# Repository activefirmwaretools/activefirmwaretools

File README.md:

# Active Firmware Tools

**Record. Reveal. Refine.**

The official repository for the Active-Pro Debugger and Logic Analyzer family — the recorder of embedded system behavior.

[Download](https://activefirmwaretools.com/download) · [User's Manual](https://activefirmwaretools.com/usersmanual) · [Store](https://activefirmwaretools.com/store) · [Blog](https://activefirmwaretools.com/active-firmware-tools-blog)

---

## What is Active-Pro?

Active-Pro is a hardware-and-software toolchain that records what your embedded system is actually doing — every signal transition, every protocol event, every stretch of idle time — and lets you replay, inspect, and share that capture later.

Think of it as Wireshark for the wires on your board. Where a logic analyzer shows you waveforms and a debugger shows you breakpoints, Active-Pro records the full behavioral trace of a running system so you can see how the pieces actually fit together over time.

Three products share the same application and capture format:

- **Active Debugger** — entry-level debug port and signal capture
- **Active-Pro** — full debugger and logic analyzer
- **Active-Pro Ultra** — super-speed capture for higher-bandwidth and longer-duration traces

All three work with the free Active-Pro application on Windows, macOS, and Linux. Run the app without hardware attached to demo every feature.

## What's in this repo

| Folder | Contents |
|---|---|
| [`active-debug-port-source-code`](./active-debug-port-source-code) | Reference source for the Active debug port |
| [`active-debugger`](./active-debugger) | Active Debugger product files and examples |
| [`active-pro-application`](./active-pro-application) | Application-side examples and resources |
| [`automation`](./automation) | Automation API command-line tool and scripting examples |
| [`custom_protocol_decoder`](./custom_protocol_decoder) | Python protocol decoders that run inside the Active-Pro application |
| [`mcp-server`](./mcp-server) | MCP server for connecting Claude and other AI clients to your captures |
| [`packet-presenter-definition-files`](./packet-presenter-definition-files) | Protocol definition files for the Packet Presenter |

## Get started

1. **Buy hardware** at [activefirmwaretools.com/store](https://activefirmwaretools.com/store), or skip ahead and use demo mode.
2. **Download the application** from [activefirmwaretools.com/download](https://activefirmwaretools.com/download) — Windows, macOS, and Linux builds available.
3. **Press Capture.** With hardware attached you'll see your signals live. Without hardware you'll get the full demo capture to explore the UI.
4. **Read the manual** at [activefirmwaretools.com/usersmanual](https://activefirmwaretools.com/usersmanual) when you're ready to go deeper.

## AI-assisted analysis

Captures export to `.aft` (Active Firmware Trace) — a plain-text format with an embedded AI context block. Copy a capture to your clipboard, paste it into any AI assistant, and ask questions about timing, protocol behavior, or anomalies in plain English.

For tighter integration, the [`mcp-server`](./mcp-server) folder contains an MCP server that lets Claude Desktop and other AI clients query your captures directly.

## Contributing

We accept changes via pull requests against `main`. See [CONTRIBUTING.md](./CONTRIBUTING.md) for the workflow and coding conventions.

For bug reports and feature requests, please open an issue.

## License

Code in this repository is licensed under the MIT License. See [LICENSE](./LICENSE) for details. Hardware, firmware images, and the Active-Pro application are commercial products and are not covered by this license.

---

Made by [Active Firmware Tools](https://activefirmwaretools.com).

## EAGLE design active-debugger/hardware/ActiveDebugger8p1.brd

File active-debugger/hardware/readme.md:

# Hardware Design for the Active Debugger

## Overview
This repository contains the hardware design files for the Active Debugger. The Active Debugger is designed to facilitate straightforward debugging of embedded systems through its single Active Debug Port. This repository is intended for engineers who wish to explore, modify, or extend the hardware design according to their needs.

## Contents
- Schematic files
- PCB layout files
- Bill of Materials (BOM)
- Gerber files
- Assembly instructions
- Documentation

## License (MIT)

Copyright (c) 2025 Active Firmware Tools

Permission is hereby granted, free of charge, to any person obtaining a copy of these hardware design files (the "Hardware"), to deal in the Hardware without restriction, including without limitation the rights to use, copy, modify, merge, publish, distribute, sublicense, and/or sell copies of the Hardware, and to permit persons to whom the Hardware is furnished to do so, subject to the following conditions:

The above copyright notice and this permission notice shall be included in all copies or substantial portions of the Hardware.

THE HARDWARE IS PROVIDED "AS IS", WITHOUT WARRANTY OF ANY KIND, EXPRESS OR IMPLIED, INCLUDING BUT NOT LIMITED TO THE WARRANTIES OF MERCHANTABILITY, FITNESS FOR A PARTICULAR PURPOSE AND NONINFRINGEMENT. IN NO EVENT SHALL THE AUTHORS OR COPYRIGHT HOLDERS BE LIABLE FOR ANY CLAIM, DAMAGES OR OTHER LIABILITY, WHETHER IN AN ACTION OF CONTRACT, TORT OR OTHERWISE, ARISING FROM, OUT OF OR IN CONNECTION WITH THE HARDWARE OR THE USE OR OTHER DEALINGS IN THE HARDWARE.

## Contributing
We welcome contributions from the community! Whether you have a fix, improvement, or new feature you'd like to add, we'd love to see your work. Please submit a pull request or open an issue to discuss what you want to change.

## Contact
For support or further information, please contact [support@activefirmwaretools.com].

## Acknowledgments
- Thanks to everyone who has contributed to refining these designs.
- Special thanks to the community members who have provided valuable feedback.

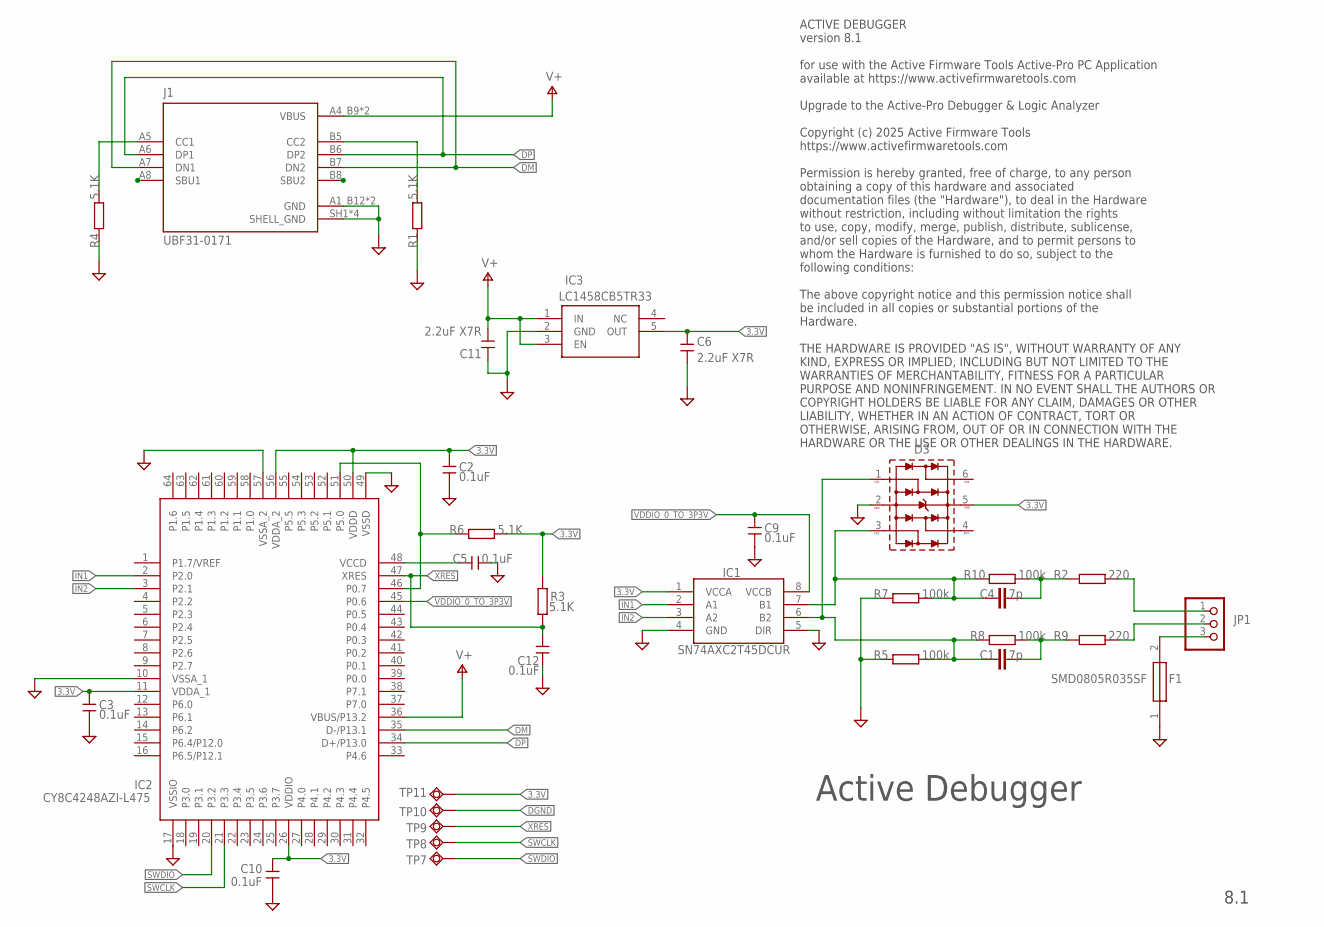
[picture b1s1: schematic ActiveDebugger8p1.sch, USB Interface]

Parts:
C1, C4: 7p; C0603
C2, C3, C5, C9, C10, C12: 0.1uF; 0603
C6, C11: 2.2uF X7R; 0805
D3: 5Vdc; WE-TVS_SC70-6L
F1: SMD0805R035SF; FUSC2114X100N
IC1: SN74AXC2T45DCUR; SOP50P310X90-8N
IC2: CY8C4248AZI-L475; QFP50P1200X1200X160-64N
IC3: LC1458CB5TR33; SOT95P280X145-5N
J1: UBF31-0171; GCT_USB4105GFA120
JP1: P125-1103A0BR138A1; 1X03
R1, R3, R4, R6: 5.1K; R0603
R2, R9: 220; R0603
R5, R7, R8, R10: 100k; R0603
TP7, TP8, TP9, TP10: TPSQTP20R; TP20R
TP11: TPSQTP20SQ; TP20SQ

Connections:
3.3V: C2.1 (X), C3.1 (X), C6.2 (Y), C10.1 (X), D3.5 (VDD), IC1.1 (VCCA), IC2.11 (VDDA_1), IC2.26 (VDDIO), IC2.50 (VDDD), IC2.56 (VDDA_2), IC3.5 (OUT), R3.2, R6.2, TP11.TP
DGND: C2.2 (Y), C3.2 (Y), C5.2 (Y), C6.1 (X), C9.2 (Y), C10.2 (Y), C11.1 (X), C12.1 (X), D3.2 (GND), F1.1, IC1.4 (GND), IC1.5 (DIR), IC2.10 (VSSA_1), IC2.17 (VSSIO), IC2.49 (VSSD), IC2.57 (VSSA_2), IC3.2 (GND), J1.A1_B12 (GND), J1.B1_A12 (GND), J1.SH1 (SHELL_GND), J1.SH2 (SHELL_GND), J1.SH3 (SHELL_GND), J1.SH4 (SHELL_GND), R1.1, R4.1, R5.1, R7.1, TP10.TP
DIN0: JP1.1, R2.2
DIN1: JP1.2, R9.2
DM: IC2.35 (D-/P13.1), J1.A7 (DN1), J1.B7 (DN2)
DP: IC2.34 (D+/P13.0), J1.A6 (DP1), J1.B6 (DP2)
DP0: C4.1, D3.3, IC1.7 (B1), R7.2, R10.1
DP1: C1.1, D3.1, IC1.6 (B2), R5.2, R8.1
IN1: IC1.2 (A1), IC2.2 (P2.0)
IN2: IC1.3 (A2), IC2.3 (P2.1)
unnamed: C4.2, R2.1, R10.2
unnamed: F1.2, JP1.3
unnamed: IC2.46 (P0.7), IC2.51 (P5.0), R6.1
unnamed: C5.1 (X), IC2.48 (VCCD)
unnamed: J1.A5 (CC1), R4.2
unnamed: J1.B5 (CC2), R1.2
unnamed: C1.2, R8.2, R9.1
SWCLK: IC2.21 (P3.3), TP8.TP
SWDIO: IC2.20 (P3.2), TP7.TP
V+: C11.2 (Y), IC2.36 (VBUS/P13.2), IC3.1 (IN), IC3.3 (EN), J1.A4_B9 (VBUS), J1.B4_A9 (VBUS)
VDDIO_0_TO_3P3V: C9.1 (X), IC1.8 (VCCB), IC2.45 (P0.6)
XRES: C12.2 (Y), IC2.47 (XRES), R3.1, TP9.TP

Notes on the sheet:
Active Debugger
ACTIVE DEBUGGER version 8.1 for use with the Active Firmware Tools Active-Pro PC Application available at https://www.activefirmwaretools.com Upgrade to the Active-Pro Debugger & Logic Analyzer Copyright (c) 2025 Active Firmware Tools https://www.activefirmwaretools.com Permission is hereby granted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
8.1

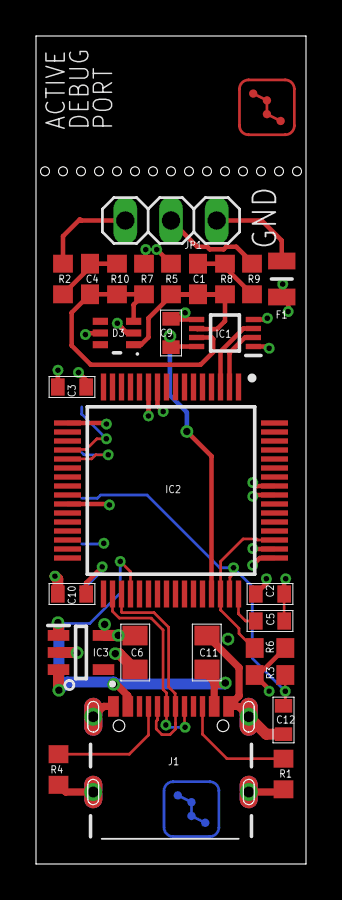
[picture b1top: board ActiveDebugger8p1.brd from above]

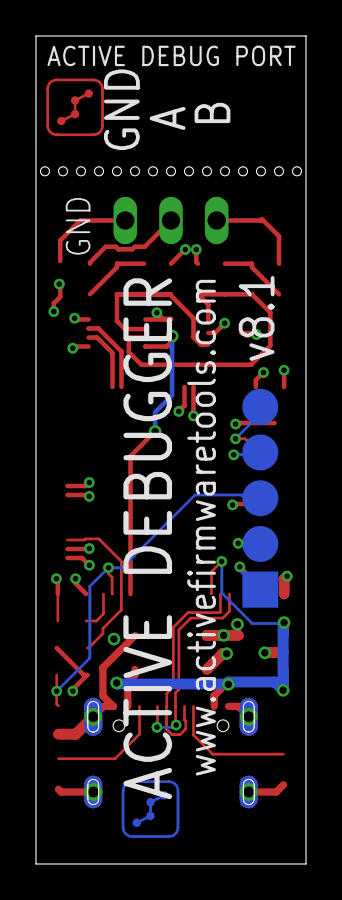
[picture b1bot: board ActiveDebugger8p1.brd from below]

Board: 4 copper layers, 15.0 x 46.0 mm, 32 parts (5 on the bottom side), 22 nets.

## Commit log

2024-12-17 Rename tmp1117-i2c-packet-presenter.txt to tmp117-i2c-packet-presenter.txt
2024-12-18 Update LICENSE
2024-12-30 Rename readme.txt to readme.md

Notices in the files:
parts and their libraries:
Wurth_EMC Components_WE-TVS: Copyright: Würth Elektronik
